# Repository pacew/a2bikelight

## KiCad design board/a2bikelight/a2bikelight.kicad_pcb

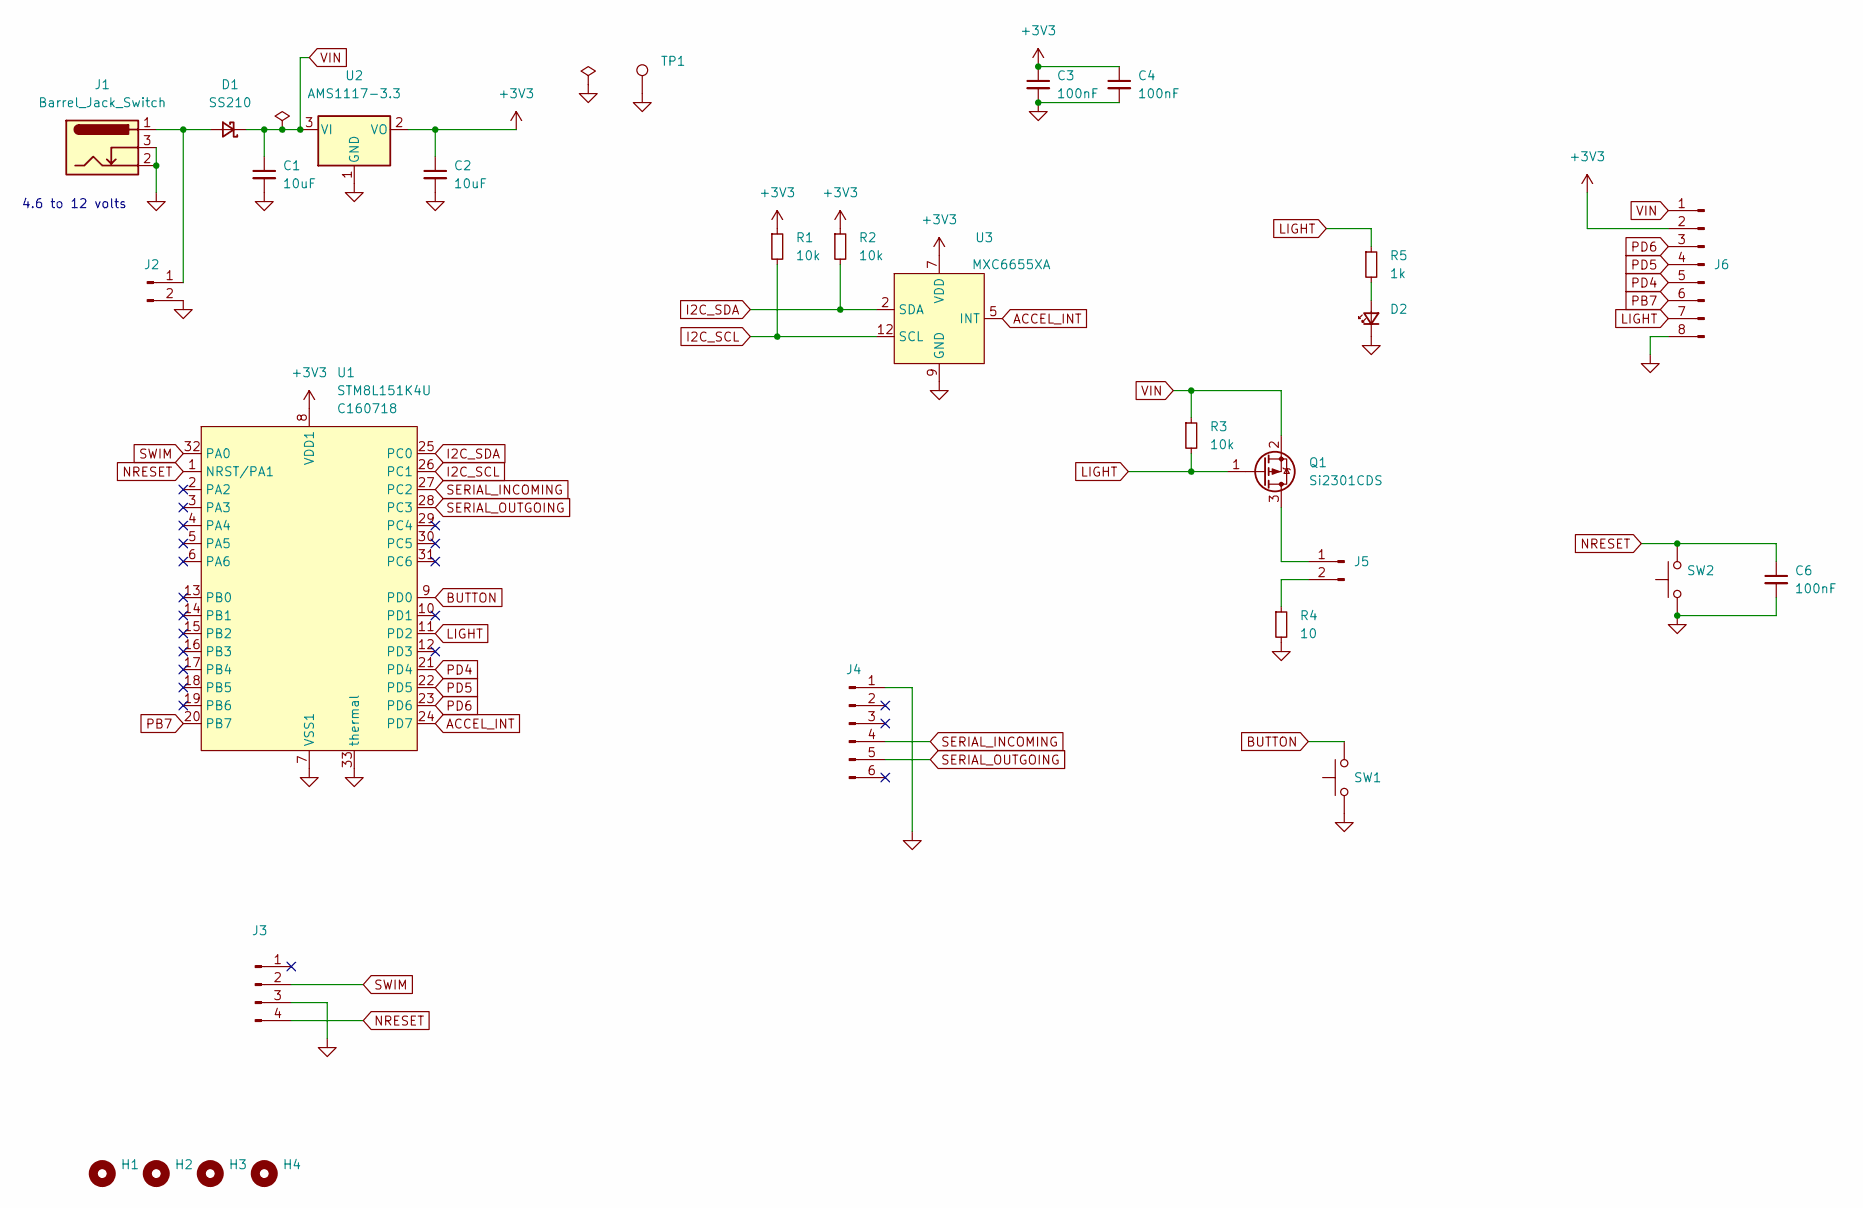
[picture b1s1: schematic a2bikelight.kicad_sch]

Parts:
C1, C2: 10uF; C_0603_1608Metric; LCSC C96446
C3, C4, C6: 100nF; C_0603_1608Metric; LCSC C14663
D1: SS210; D_SMA; LCSC C14996
D2: LED_Small; LED_0805_2012Metric; LCSC C2297
H1, H2, H3, H4: MountingHole; MountingHole_3.5mm
J1: Barrel_Jack_Switch; BarrelJack_Horizontal
J2, J5: Conn_01x02_Male; PinHeader_1x02_P2.54mm_Vertical
J3: Conn_01x04_Male; PinHeader_1x04_P2.54mm_Vertical
J4: Conn_01x06_Male; PinHeader_1x06_P2.54mm_Vertical
J6: Conn_01x08_Male; PinHeader_1x08_P2.54mm_Vertical
Q1: Si2301CDS; SOT-23; LCSC C10487
R1, R2: 10k; R_0603_1608Metric; LCSC C25804
R3: 10k; R_0805_2012Metric; LCSC C17414
R4: 10; R_2512_6332Metric; LCSC C16861
R5: 1k; R_0603_1608Metric; LCSC C21190
SW1, SW2: SW_Push; SW_PUSH_6mm
TP1: TestPoint; TestPoint_THTPad_2.0x2.0mm_Drill1.0mm
U1: STM8L151K4U; UFQFPN-32_5x5_Pitch0.5mm; LCSC C160718
U2: AMS1117-3.3; SOT-223-3_TabPin2; LCSC C6186
U3: MXC6655XA; LGA-12_2x2mm_P0.5mm; LCSC C5189050

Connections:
+3V3: C2.1, C3.1, C4.1, J6.2, R1.1, R2.1, U1.8 (VDD1), U2.2 (VO), U3.7 (VDD)
ACCEL_INT: U1.24 (PD7), U3.5 (INT)
BUTTON: SW1.2, U1.9 (PD0)
GND: C1.2, C2.2, C3.2, C4.2, C6.2, D2.1 (K), J1.2, J1.3, J2.2, J3.3, J4.1, J6.8, R4.2, SW1.1, SW2.1, TP1.1, U1.7 (VSS1), U1.33 (thermal), U2.1 (GND), U3.9 (GND)
I2C_SCL: R1.2, U1.26 (PC1), U3.12 (SCL)
I2C_SDA: R2.2, U1.25 (PC0), U3.2 (SDA)
LIGHT: J6.7, Q1.1 (G), R3.2, R5.1, U1.11 (PD2)
NRESET: C6.1, J3.4, SW2.2, U1.1 (NRST/PA1)
unnamed: D1.2 (A), J1.1, J2.1
unnamed: D2.2 (A), R5.2
unnamed: J5.1, Q1.3 (D)
unnamed: J5.2, R4.1
PB7: J6.6, U1.20 (PB7)
PD4: J6.5, U1.21 (PD4)
PD5: J6.4, U1.22 (PD5)
PD6: J6.3, U1.23 (PD6)
SERIAL_INCOMING: J4.4, U1.27 (PC2)
SERIAL_OUTGOING: J4.5, U1.28 (PC3)
SWIM: J3.2, U1.32 (PA0)
VIN: C1.1, D1.1 (K), J6.1, Q1.2 (S), R3.1, U2.3 (VI)

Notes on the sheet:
4.6 to 12 volts

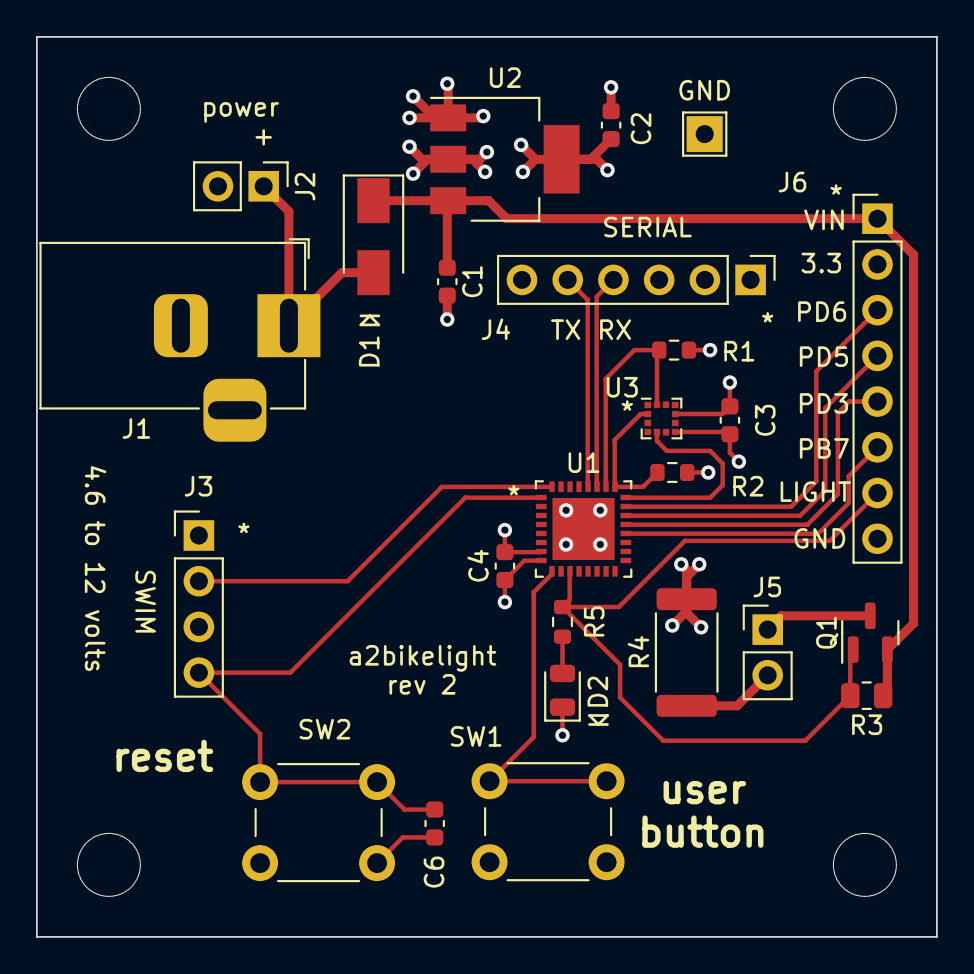
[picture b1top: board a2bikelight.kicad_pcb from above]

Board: 4 copper layers, 50.0 x 50.0 mm, 29 parts (0 on the bottom side), 20 nets.

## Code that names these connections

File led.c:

/*
 * using stm8l151k4
 * "medium density"
 * 16k flash
 * 1k eeprom
 * 2k ram
 * 1 basic 8 bit timer
 * 2 general purpose 16 bit timers
 * 1 advanced control 16 bit timer
 * 1 spi
 * 1 i2c
 * 1 usart
 */



#include <stdint.h>
#include <stdio.h>

#define PC_ODR	(*(volatile uint8_t *)0x500a)
#define PC_DDR	(*(volatile uint8_t *)0x500c)
#define PC_CR1	(*(volatile uint8_t *)0x500d)

#define PD_ODR	(*(volatile uint8_t *)0x500f)
#define PD_DDR	(*(volatile uint8_t *)0x5011)
#define PD_CR1	(*(volatile uint8_t *)0x5012)

#define PE_ODR	(*(volatile uint8_t *)0x5014)
#define PE_DDR	(*(volatile uint8_t *)0x5016)
#define PE_CR1	(*(volatile uint8_t *)0x5017)

#define CLK_DIVR	(*(volatile uint8_t *)0x50c0)
#define CLK_PCKENR1	(*(volatile uint8_t *)0x50c3)
#define CLK_PCKENR2	(*(volatile uint8_t *)0x50c4)

#define TIM1_CR1	(*(volatile uint8_t *)0x52b0)
#define TIM1_PCNTRH	(*(volatile uint8_t *)0x52bf)
#define TIM1_PCNTRL	(*(volatile uint8_t *)0x52c0)
#define TIM1_PSCRH	(*(volatile uint8_t *)0x52c1)
#define TIM1_PSCRL	(*(volatile uint8_t *)0x52c2)

#define USART1_SR (*(volatile uint8_t *)0x5230) // USART1 status register
#define USART1_DR (*(volatile uint8_t *)0x5231) // USART1 data register
#define USART1_BRR1 (*(volatile uint8_t *)0x5232) // USART1 baud rate register 1
#define USART1_BRR2 (*(volatile uint8_t *)0x5233) // USART1 baud rate register 2
#define USART1_CR1 (*(volatile uint8_t *)0x5234) // USART1 control register 1
#define USART1_CR2 (*(volatile uint8_t *)0x5235) // USART1 control register 2
#define USART1_CR3 (*(volatile uint8_t *)0x5236) // USART1 control register 3
#define USART1_CR4 (*(volatile uint8_t *)0x5237) // USART1 control register 4
#define USART1_CR5 (*(volatile uint8_t *)0x5238) // USART1 control register 5
#define USART1_GTR (*(volatile uint8_t *)0x5239) // USART1 guard time register
#define USART1_PSCR (*(volatile uint8_t *)0x523A) // USART1 prescaler register

#define GPIO_BASE(port) (0x5000 + 5 * ((port) - 'A'))

#define GPIO_MASK(bitnum) (1 << (bitnum))

#define GPIO_ODR(port) (*(volatile uint8_t *)(GPIO_BASE(port) + 0))
#define GPIO_IDR(port) (*(volatile uint8_t *)(GPIO_BASE(port) + 1))
#define GPIO_DDR(port) (*(volatile uint8_t *)(GPIO_BASE(port) + 2))
#define GPIO_CR1(port) (*(volatile uint8_t *)(GPIO_BASE(port) + 3))
#define GPIO_CR2(port) (*(volatile uint8_t *)(GPIO_BASE(port) + 4))

#define GPIO_SET(port, bitnum) (GPIO_ODR(port) |= GPIO_MASK(bitnum))
#define GPIO_CLEAR(port, bitnum) (GPIO_ODR(port) &= ~GPIO_MASK(bitnum))


/*
 * STM8L151K4U6TR
 * UFQFPN-32(5x5)
 * use table 5, Medium density STM8L151x4/6, 2nd column "LQFP32/UFQFPN32"
 */

/* D3 on pin 12. functions: PD3/TIM1_ETR/LCD_SEG9/ADC1_IN19/COMP1_INP */
#define LIGHT_PORT 'D'
#define LIGHT_BITNUM 3


#define TIM1_CR1 (*(volatile uint8_t *)0x52b0)
#define TIM1_CR2 (*(volatile uint8_t *)0x52b1)
#define TIM1_SMCR (*(volatile uint8_t *)0x52b2)
#define TIM1_ETR (*(volatile uint8_t *)0x52b3)
#define TIM1_DER (*(volatile uint8_t *)0x52b4)
#define TIM1_IER (*(volatile uint8_t *)0x52b5)
#define TIM1_SR1 (*(volatile uint8_t *)0x52b6)
#define TIM1_SR2 (*(volatile uint8_t *)0x52b7)
#define TIM1_EGR (*(volatile uint8_t *)0x52b8)
#define TIM1_CCMR1 (*(volatile uint8_t *)0x52b9)
#define TIM1_CCMR2 (*(volatile uint8_t *)0x52ba)
#define TIM1_CCMR3 (*(volatile uint8_t *)0x52bb)
#define TIM1_CCMR4 (*(volatile uint8_t *)0x52bc)
#define TIM1_CCER1 (*(volatile uint8_t *)0x52bd)
#define TIM1_CCER2 (*(volatile uint8_t *)0x52be)
#define TIM1_CNTRH (*(volatile uint8_t *)0x52bf)
#define TIM1_CNTRL (*(volatile uint8_t *)0x52c0)
#define TIM1_PSCRH (*(volatile uint8_t *)0x52c1)
#define TIM1_PSCRL (*(volatile uint8_t *)0x52c2)
#define TIM1_ARRH (*(volatile uint8_t *)0x52c3)
#define TIM1_ARRL (*(volatile uint8_t *)0x52c4)
#define TIM1_RCR (*(volatile uint8_t *)0x52c5)
#define TIM1_CCR1H (*(volatile uint8_t *)0x52c6)
#define TIM1_CCR1L (*(volatile uint8_t *)0x52c7)
#define TIM1_CCR2H (*(volatile uint8_t *)0x52c8)
#define TIM1_CCR2L (*(volatile uint8_t *)0x52c9)
#define TIM1_CCR3H (*(volatile uint8_t *)0x52ca)
#define TIM1_CCR3L (*(volatile uint8_t *)0x52cb)
#define TIM1_CCR4H (*(volatile uint8_t *)0x52cc)
#define TIM1_CCR4L (*(volatile uint8_t *)0x52cd)
#define TIM1_BKR (*(volatile uint8_t *)0x52ce)
#define TIM1_DTR (*(volatile uint8_t *)0x52cf)
#define TIM1_OISR (*(volatile uint8_t *)0x52d0)
#define TIM_DCR1 (*(volatile uint8_t *)0x52d1)
#define TIM1_DCR2 (*(volatile uint8_t *)0x52d2)
#define TIM1_DMA1R (*(volatile uint8_t *)0x52d3)

void
gpio_init_output (uint8_t port, uint8_t bitnum)
{
	GPIO_DDR(port) |= GPIO_MASK(bitnum); // output
	GPIO_CR1(port) |= GPIO_MASK(bitnum); // push-pull
	GPIO_CR2(port) &= ~GPIO_MASK(bitnum); // low speed (up to 2 MHz)
}

unsigned int
clock(void)
{
	unsigned char h = TIM1_PCNTRH;
	unsigned char l = TIM1_PCNTRL;
	return((unsigned int)(h) << 8 | l);
}

int
putchar (int c)
{
	if (c == '\n') {
		while ((USART1_SR & 0x80) == 0) // TXE Transmit data empty
			;
		USART1_DR = '\r';
	}
	while ((USART1_SR & 0x80) == 0) // TXE Transmit data empty
		;
	USART1_DR = c;
	return (c);
}


void
delay(int count)
{
	unsigned int start, now, delta;

	start = clock();
	while (1) {
		now = clock();
		delta = now - start;
		if (delta >= count)
			break;
	}
}

void blink (void);
void pwm (void);

void
main(void)
{
	CLK_DIVR = 0x00; // Set the frequency to 16 MHz
	CLK_PCKENR2 |= 0x02; // Enable clock to TIM1

	/* 
	 * serial 
	 * incoming PC2, pin 27
	 * outgoing PC3, pin28
	 */
	CLK_PCKENR1 |= 0x20; // Enable clock to usart1

	/* adafruit: white is data to usb; green is data from usb */
	/* 16MHz, 9600 bit/s USART_DIV  0x0683 */
	USART1_BRR1 = 0x68;
	USART1_BRR2 = 0x3;

	USART1_CR2 |= 0x0c; // transmitter enable + receiver enable

	gpio_init_output (LIGHT_PORT, LIGHT_BITNUM);

	pwm ();
}

void
blink (void)
{
	// Configure timer for delay use (overridden by pwm)
	// 1000 ticks per second
	TIM1_PSCRH = 0x3e;
	TIM1_PSCRL = 0x80;
	// Enable timer
	TIM1_CR1 = 0x01;


	int val = 0;
	while (1) {
		GPIO_CLEAR(LIGHT_PORT, LIGHT_BITNUM); // off
		delay (400);
		GPIO_SET(LIGHT_PORT, LIGHT_BITNUM); // on
		delay (100);
		val++;
		printf ("hello %d\n", val);
	}
}

/* D4 on pin 21. functions: PD4/TIM1_CH2/LCD_SEG18/ADC1_IN10/COMP1_INP */
#define PWM_PORT 'D'
#define PWM_BITNUM 4

void
pwm (void)
{
	GPIO_CR1(PWM_PORT) |= GPIO_MASK(PWM_BITNUM); // push pull

/*
Up-counting is active when the DIR bit in the TIM1_CR1 register is
low.  Example This example uses PWM mode 1. The reference PWM signal,
OCiREF, is high as long as TIM1_CNT < TIM1_CCRi. Otherwise, it becomes
low. If the compare value in TIM1_CCRi is greater than the auto-reload
value (in TIM1_ARR) then OCiREF is held at 1. If the compare value is
0, OCiREF is held at 0. Figure 106 shows some edge-aligned PWM
waveforms in an example where TIM1_ARR = 8.
*/
	
	TIM1_CCMR2 = (TIM1_CCMR2 & ~0x03) | 0x00; /* CC2S = 0 for output */
	TIM1_CCMR2 = (TIM1_CCMR2 & ~0x70) | 0x60; /* OC2M: PWM mode 1 */
	TIM1_CCMR2 &= ~3; // output

	TIM1_CCER2 |= 1; /* CC2E */

	TIM1_CCER1 |= 0x10; // CC2NE

	uint16_t prescale = 0;
	TIM1_PSCRH = prescale >> 8;
	TIM1_PSCRL = prescale & 0xff;

	int reload = 160;
	TIM1_ARRH = reload >> 8;
	TIM1_ARRL = reload & 0xff;

	int compare = 100;
	TIM1_CCR2H = compare >> 8;
	TIM1_CCR2L = compare & 0xff;

	TIM1_BKR |= 0x80; /* MOE = 1 */

	TIM1_CR1 |= 1; /* CEN counter enable */

	int val = 0;
	int last = 0;
	while (1) {
		val++;
		uint8_t hi = TIM1_CNTRH;
		uint8_t lo = TIM1_CNTRL;
		uint16_t count = (hi << 8) | lo;

		printf ("hello %d %5d %6d %02x\n", 
			val, count, count - last,
			TIM1_SR1);
		if (TIM1_SR1 & 1) {
			printf ("tick %02x **************************\n",
 				TIM1_SR1);
			TIM1_SR1 &= ~1;
		}
		if (TIM1_SR1 & 4) {
			printf ("tock %02x *************\n",
 				TIM1_SR1);
			TIM1_SR1 &= ~4;
		}
		last = count;
			

	}

}

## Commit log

2023-02-18 notes
2023-02-18 start
2023-02-19 docs
2023-02-19 footprint
2023-02-19 gitignore
2023-02-21 baseline
2023-02-23 layout
2023-02-23 rev1
2023-03-09 led flashes on proto board
2023-03-15 print
2023-03-15 printf
2023-03-15 size
2023-04-02 gpio
2023-04-02 counter counts
2023-04-02 100k
2023-05-10 rev2
2023-10-25 kicad 7; fabrication outputs
